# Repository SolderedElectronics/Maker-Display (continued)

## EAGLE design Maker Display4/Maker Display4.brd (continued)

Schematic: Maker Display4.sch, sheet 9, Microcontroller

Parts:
C1, C3, C8: 2.2uF; 0603
C4: 0.1uF; 0603
D1: BAT20J; SOD-323
J3: QWIIC_CONNECTORJS-1MM; 1X04_1MM_RA
JP1: M02-JST-2MM-SMT; JST-2-SMD
LED1: LEDCHIPLED_0805; CHIPLED_0805
Q3: PMOS; SOT23-3
R9, R10, R12, R18, R19, R20: 10k; 0603
R11: 20k; 0603
R13, R16: 2.49k; 0603
R17: 1k; 0603
S1: SWITCH_SK-12D02-VG5; SK-12D02-VG5
U1: MCP73831; SOT23-5
U$3: ESP-PROGRAMMINGPORT; ESP-PROGRAMMING-PORT
U$6, U$16, U$18, U$19, U$20, U$21: PAD-1
U$9: SE5218; SOT23-5
U$15: USB-MICRO; U-F-M5DD-Y-L
X1: ESP8266-12; ESP-12

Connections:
3.3V: C3.1, C4.1, J3.2, R10.2, R18.2, R19.2, R20.2, U$3.2 (VCC), U$9.5 (VOUT), U$20.1, X1.8 (VCC)
ADC: R12.1, R13.2, X1.2 (ADC)
CH_PD: R18.1, X1.3 (CH_PD)
GND: C1.2, C3.2, C4.2, C8.2, J3.1, JP1.1, R9.1, R11.1, R13.1, R16.2, U1.2 (VSS), U$3.1 (GND), U$9.2 (GND), U$15.5 (GND), U$15.PAD (GND), U$15.SHIELD1 (GND), U$15.SHIELD2 (GND), U$15.SHIELD3 (GND), U$15.SHIELD4 (GND), U$21.1, X1.9 (GND); also elsewhere on the board
GPIO0: R20.1, U$3.6 (RESET), X1.12 (GPIO0)
GPIO2: R10.1, X1.11 (GPIO2)
GPIO12: U$18.1, X1.6 (GPIO12)
GPIO13: U$19.1, X1.7 (GPIO13)
GPIO14: U$16.1, X1.5 (GPIO14)
GPIO15: R9.2, X1.10 (GPIO15)
GPIO16: U$6.1, X1.4 (GPIO16)
unnamed: D1.C, Q3.2 (S), S1.2
unnamed: R16.1, U1.5 (PROG)
unnamed: LED1.C, U1.1 (STAT)
unnamed: LED1.A, R17.2
RESET: R19.1, U$3.5 (GPIO0), X1.1 (RESET)
RXD: U$3.4 (RX), X1.15 (RXD)
SCL: J3.4, X1.14 (GPIO4); also elsewhere on the board
SDA: J3.3, X1.13 (GPIO5); also elsewhere on the board
TXD: U$3.3 (TX), X1.16 (TXD)
VCC: C1.1, S1.3, U$9.1 (VIN), U$9.3 (EN); also elsewhere on the board
V_BATT: C8.1, JP1.2, Q3.3 (D), R12.2, U1.3 (VBAT)
V_USB: D1.A, Q3.1 (G), R11.2, R17.1, U1.4 (VIN), U$15.1 (VBUS)

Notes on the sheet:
USB connector and voltage regulator
ESP12(-E)
Default pull up & pull down resistors
v1.0
Power source selection & battery connector
Lithium battery charger
easyC

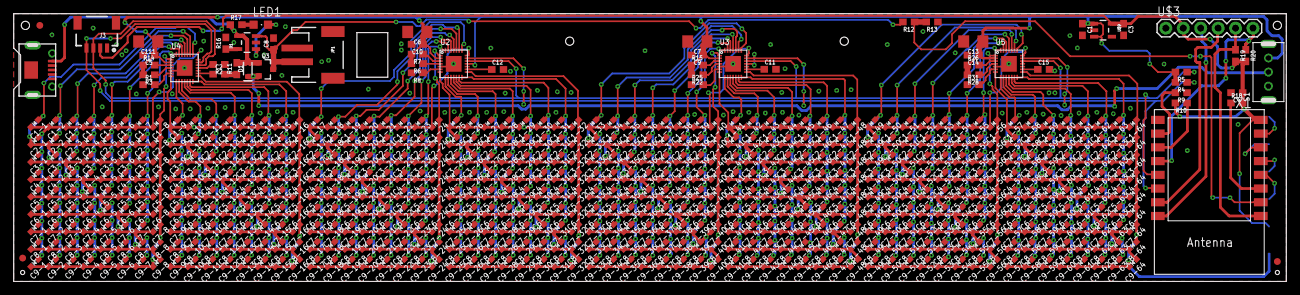
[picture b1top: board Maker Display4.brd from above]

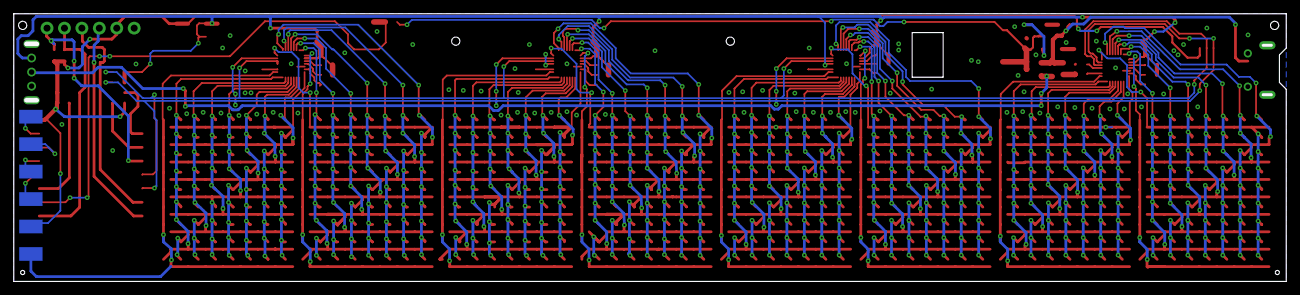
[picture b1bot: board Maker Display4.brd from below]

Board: 2 copper layers, 185.4 x 39.0 mm, 648 parts (6 on the bottom side), 112 nets.

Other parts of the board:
U$23: EASYC
U$24: LOGO-6MM
U$25: E-R.IO-6MM
U$26: OSH-3MM
U$27: MAKER-DISPLAY-LOGO-BIG
U$28: LOGO-BACK-12MM
U$29: E-R.IO-BACK-12MM

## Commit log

2019-02-12 Initial
2019-02-12 add readme
